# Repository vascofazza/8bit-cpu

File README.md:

# MK1 8bit Computer

Schematics and code for my home-made 8-bit CPU and its companion boards.

Articles about this project:

[Hackaday.com](https://hackaday.com/2020/12/31/diy-8-bit-computer-knows-all-the-tricks/)

[Hackster.io](https://www.hackster.io/news/see-inside-of-a-cpu-with-the-mk1-8bit-computer-14fa9e313c73)

[InformaticaLab.com](https://blog.informaticalab.com/viaggio-allinterno-di-una-cpu-con-il-mk1-8bit-computer/)

## Overview

During the past month, I designed and built a programmable 8-bit CPU from scratch, out of basic series 74LS logic ICs.

This repository contains pictures, schematics, and code for this project and its companion boards.

* V 1.0 assembled:

* V 2.0b assembled:

- Helix Display Interface in action:

* V 1.0 in action:

**DEMO VIDEO (YouTube)**

## Architecture

The MK1 CPU is composed of several modules, all connected trough a common 8-bit BUS, the status of each module is shown by dedicated LEDs. 

- The clock module is designed to allow step-by-step execution; in automatic mode the clock speed can be adjusted from 1Hz up to 32KHz.
- The computer programs are stored in RAM and the CPU can be programmed both manually, by inserting binary machine code through dip-switches, and automatically via a USB PC interface. 
  - The Programming interface is designed to be used in conjunction with an **Arduino Nano** or the **Start9** programming board.
  - The **Start9** programming board allows the loading of multiple programs stored on an on-board flash memory without the aid of an external computer device.
- The Addressable memory space is 1024 byte, data, stack and code spaces are separated, the code address space is not writable. 
- The instructions are variable-length (see **instruction-set [here](https://github.com/vascofazza/8bit-cpu/tree/master/MK1_CPU/programs/lib/mk1.cpu)**) 1 or 2 bytes long (first byte for the opcode, the second one for the argument), there are 4 general purpose registers (`A`, `B`, `C`, `D`) and a  `stack pointer` register for subroutine calls.
- The **A**rithmetic **L**ogic **U**nit has a dedicated register for the second operand and supports the following operations:
  - Addition
  - Subtraction
  - OR
  - AND
  - NOT
  - Left/Right Shift
  - Left/Right Rotation
- The Control Unit combinatory logic is implemented using EEPROMs (see **microcode [here](https://github.com/vascofazza/8bit-cpu/blob/master/MK1_CPU/code/microcode.txt)**) whilst each instruction is realized through a variable number of micro-instruction for a maximum of 6 micro-steps per instruction, including the fetch cycle. The instruction-set  supports both direct and indirect memory access as well as absolute and conditional jumps on carry (`CF`) and zero (`ZF`) ALU flags.
- The computation output can be visualized on a 4-digit display, with a dedicated register, able to represent positive and 2-complement negative numbers both in decimal and hexadecimal format.
- The CPU can be extended thanks to the external BUS interface capable of handling up to 2 peripheral. The communication is bidirectional, the devices can send interrupts to the CPU to notify when new data is available. Interrupts are cleared once the data has been processed.
  - The only available peripheral at the moment is the **Helix** display interface, an ATmega328-driven 2x16 LCD output display.

## Structure

- **MK1 CPU/**:
  - **8bit-computer/**: KiCad project, schematics and PCB design of the **MK1 CPU**.
  - **code/**:
    - microcode.py: generates the binary EEPROM microcode.
    - out_display.py: generates the binary output display EEPROM code.
    - uploader.py: uploads a binary MK1 program to the CPU.
    - mk1_computer_uploader/: Arduino programmer interface sketch.
  - **assembler/**: fork of the hlorenzi's assembler, improved and customized for the MK1
  - **programs/**: a collection of programs for the MK1 CPU plus the assembler definition
- **start9_programming_interface/**: 
  - **programming_interface/**: KiCad project, schematics and PCB design of the **Start9** programming board.
  - **code/start9_programming_interface/**: Arduino code for the programming interface.
- **helix_display_interface/**:
  - **display_interface/**: KiCad project, schematics and PCB design of the **Helix** display interface board.
  - **code/helix_display_interface/**: Arduino code for the display interface.
- **eeprom_programmer/**: KiCad project, schematics and PCB design of a simple Arduino-based eeprom programmer
- **bus_breakout/**: KiCad project, schematics and PCB design of the external bus connector breakout board.

## Changelog

##### V2.0d:

- minor hardware revision
- revisited PCB design
- new memory architecture, code memory section is read-only, stack and data live on separated spaces

##### V2.0b:

- minor hardware revision
- Variable-length instructions (1 or 2 bytes)
- new custom assembler, thanks to https://github.com/hlorenzi/customasm
- few new instructions
- revisited microcode and instruction-set

##### V2.0:

- 4 general purposes registers (A, B, C, D)
- Stack Pointer implemented as an up-down counter
- External interface and interrupt handling
- Output display decodes HEX and ASCII values
- Clock speed multipliers
- Control Unit extended with 4 EEPROMs
- Variable step microcode counter length (each instruction uses the minimum amount of micro-steps)
- revisited microcode and instruction-set

##### V1.0:

- Bugfixes.
- `HL` and `STK` address signals available in the `MAR` dip-switch.

##### V0.1:

- Initial release

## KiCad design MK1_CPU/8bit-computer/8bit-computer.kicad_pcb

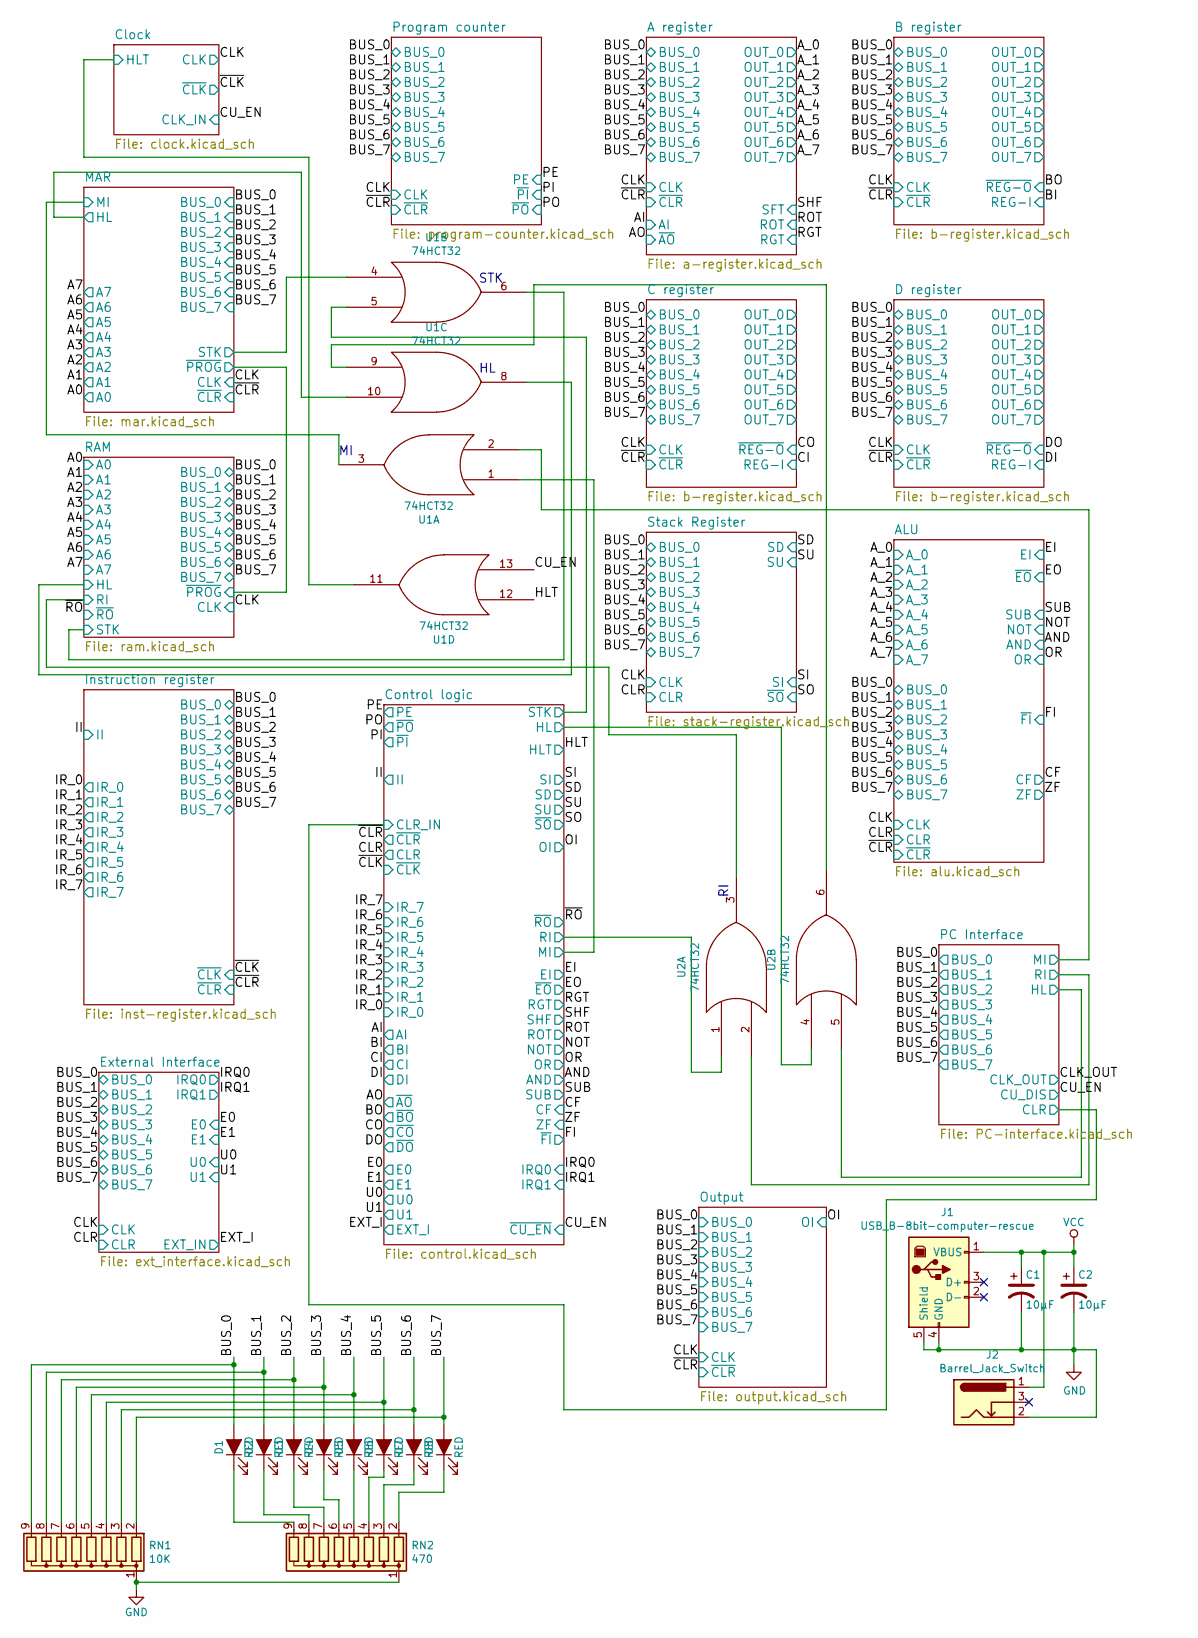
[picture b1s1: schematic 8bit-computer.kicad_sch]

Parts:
C1, C2: 10µF; CP_Radial_D5.0mm_P2.00mm
D1, D2, D3, D4, D5, D6, D7, D8: RED; LED_D3.0mm
J1: USB_B-8bit-computer-rescue; USB_B_OST_USB-B1HSxx_Horizontal
J2: Barrel_Jack_Switch; BarrelJack_Horizontal
RN1: 10K; R_Array_SIP9
RN2: 470; R_Array_SIP9
U1, U2: 74HCT32; DIP-14_W7.62mm

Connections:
/BUS_4: D5.2 (A), RN1.5 (R4); also elsewhere on the board
/BUS_5: D6.2 (A), RN1.4 (R3); also elsewhere on the board
/BUS_6: D7.2 (A), RN1.3 (R2); also elsewhere on the board
/BUS_7: D8.2 (A), RN1.2 (R1); also elsewhere on the board
/Clock/HLT: U1.11; also elsewhere on the board
/Control logic/HL: U2.4; also elsewhere on the board
/Control logic/MI: U1.1; also elsewhere on the board
/Control logic/RI: U2.1; also elsewhere on the board
/Control logic/STK: U1.5; also elsewhere on the board
/MAR/HL: U1.10; also elsewhere on the board
/MAR/MI: U1.3; also elsewhere on the board
/MAR/STK: U1.4; also elsewhere on the board
/PC Interface/CU_DIS: U1.13; also elsewhere on the board
/PC Interface/HL: U2.5; also elsewhere on the board
/PC Interface/MI: U1.2; also elsewhere on the board
/PC Interface/RI: U2.2; also elsewhere on the board
/RAM/HL: U1.8; also elsewhere on the board
/RAM/RI: U2.3; also elsewhere on the board
/RAM/STK: U1.6; also elsewhere on the board
unnamed: D1.1 (K), RN2.9 (R8)
unnamed: D2.1 (K), RN2.8 (R7)
unnamed: D3.1 (K), RN2.7 (R6)
unnamed: D4.1 (K), RN2.6 (R5)
unnamed: D5.1 (K), RN2.5 (R4)
unnamed: D6.1 (K), RN2.4 (R3)
unnamed: D7.1 (K), RN2.3 (R2)
unnamed: D8.1 (K), RN2.2 (R1)
unnamed: U1.9, U2.6

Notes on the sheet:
STK

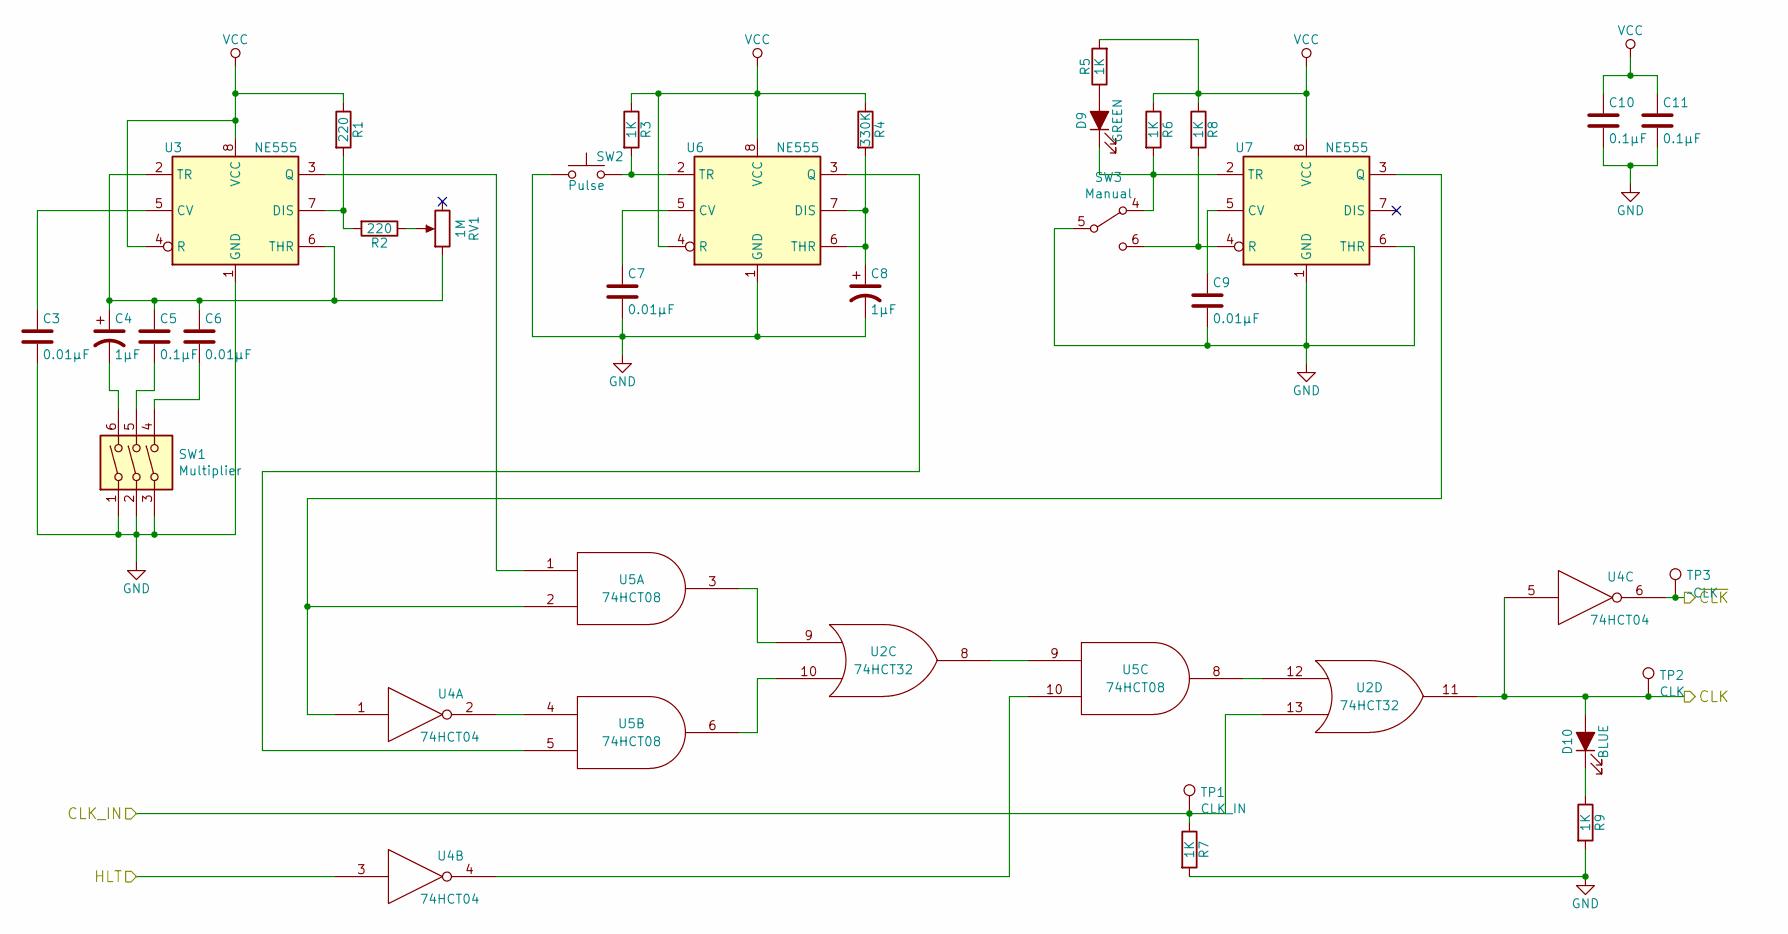
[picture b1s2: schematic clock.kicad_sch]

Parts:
C3, C6, C7, C9: 0.01µF; C_Disc_D4.3mm_W1.9mm_P5.00mm
C4, C8: 1µF; CP_Radial_D5.0mm_P2.00mm
C5, C10, C11: 0.1µF; C_Disc_D4.3mm_W1.9mm_P5.00mm
D9: GREEN; LED_D3.0mm
D10: BLUE; LED_D3.0mm
R1, R2: 220; R_Axial_DIN0207_L6.3mm_D2.5mm_P7.62mm_Horizontal
R3, R5, R6, R7, R8, R9: 1K; R_Axial_DIN0207_L6.3mm_D2.5mm_P7.62mm_Horizontal
R4: 330K; R_Axial_DIN0207_L6.3mm_D2.5mm_P7.62mm_Horizontal
RV1: 1M; Potentiometer_Bourns_PTV09A-1_Single_Vertical
SW1: Multiplier; SW_DIP_SPSTx03_Slide_9.78x9.8mm_W7.62mm_P2.54mm
SW2: Pulse; SW_PUSH_6mm_H5mm
SW3: Manual; SW_NKK_GW12LJP
TP1: CLK_IN; TestPoint_Pad_1.0x1.0mm
TP2: CLK; TestPoint_Pad_1.0x1.0mm
TP3: ~CLK; TestPoint_Pad_1.0x1.0mm
U2: 74HCT32; DIP-14_W7.62mm
U3, U6, U7: NE555; DIP-8_W7.62mm
U4: 74HCT04; DIP-14_W7.62mm
U5: 74HCT08; DIP-14_W7.62mm

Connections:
/Clock/CLK_IN: R7.1, TP1.1, U2.13; also elsewhere on the board
/Clock/HLT: U4.3; also elsewhere on the board
/~CLK: TP3.1, U4.6; also elsewhere on the board
unnamed: C3.1, U3.5 (CV)
unnamed: C4.1, C5.1, C6.1, RV1.1, U3.2 (TR), U3.6 (THR)
unnamed: C4.2, SW1.6
unnamed: C5.2, SW1.5
unnamed: C6.2, SW1.4
unnamed: C7.1, U6.5 (CV)
unnamed: C8.1, R4.2, U6.6 (THR), U6.7 (DIS)
unnamed: C9.1, U7.5 (CV)
unnamed 127: U5.11; also elsewhere on the board
unnamed: D9.1 (K), R6.2, SW3.4 (A), U7.2 (TR)
unnamed: D9.2 (A), R5.1
unnamed: D10.1 (K), R9.1
unnamed: R1.2, R2.2, U3.7 (DIS)
unnamed: R2.1, RV1.2
unnamed: R3.2, SW2.2, U6.2 (TR)
unnamed: R8.2, SW3.6 (C), U7.4 (R)
unnamed: U2.8, U5.9
unnamed: U2.9, U5.3
unnamed: U2.10, U5.6
unnamed: U2.12, U5.8
unnamed: U3.3 (Q), U5.1
unnamed: U4.1, U5.2, U7.3 (Q)
unnamed: U4.2, U5.4
unnamed: U4.4, U5.10
unnamed: U5.5, U6.3 (Q)

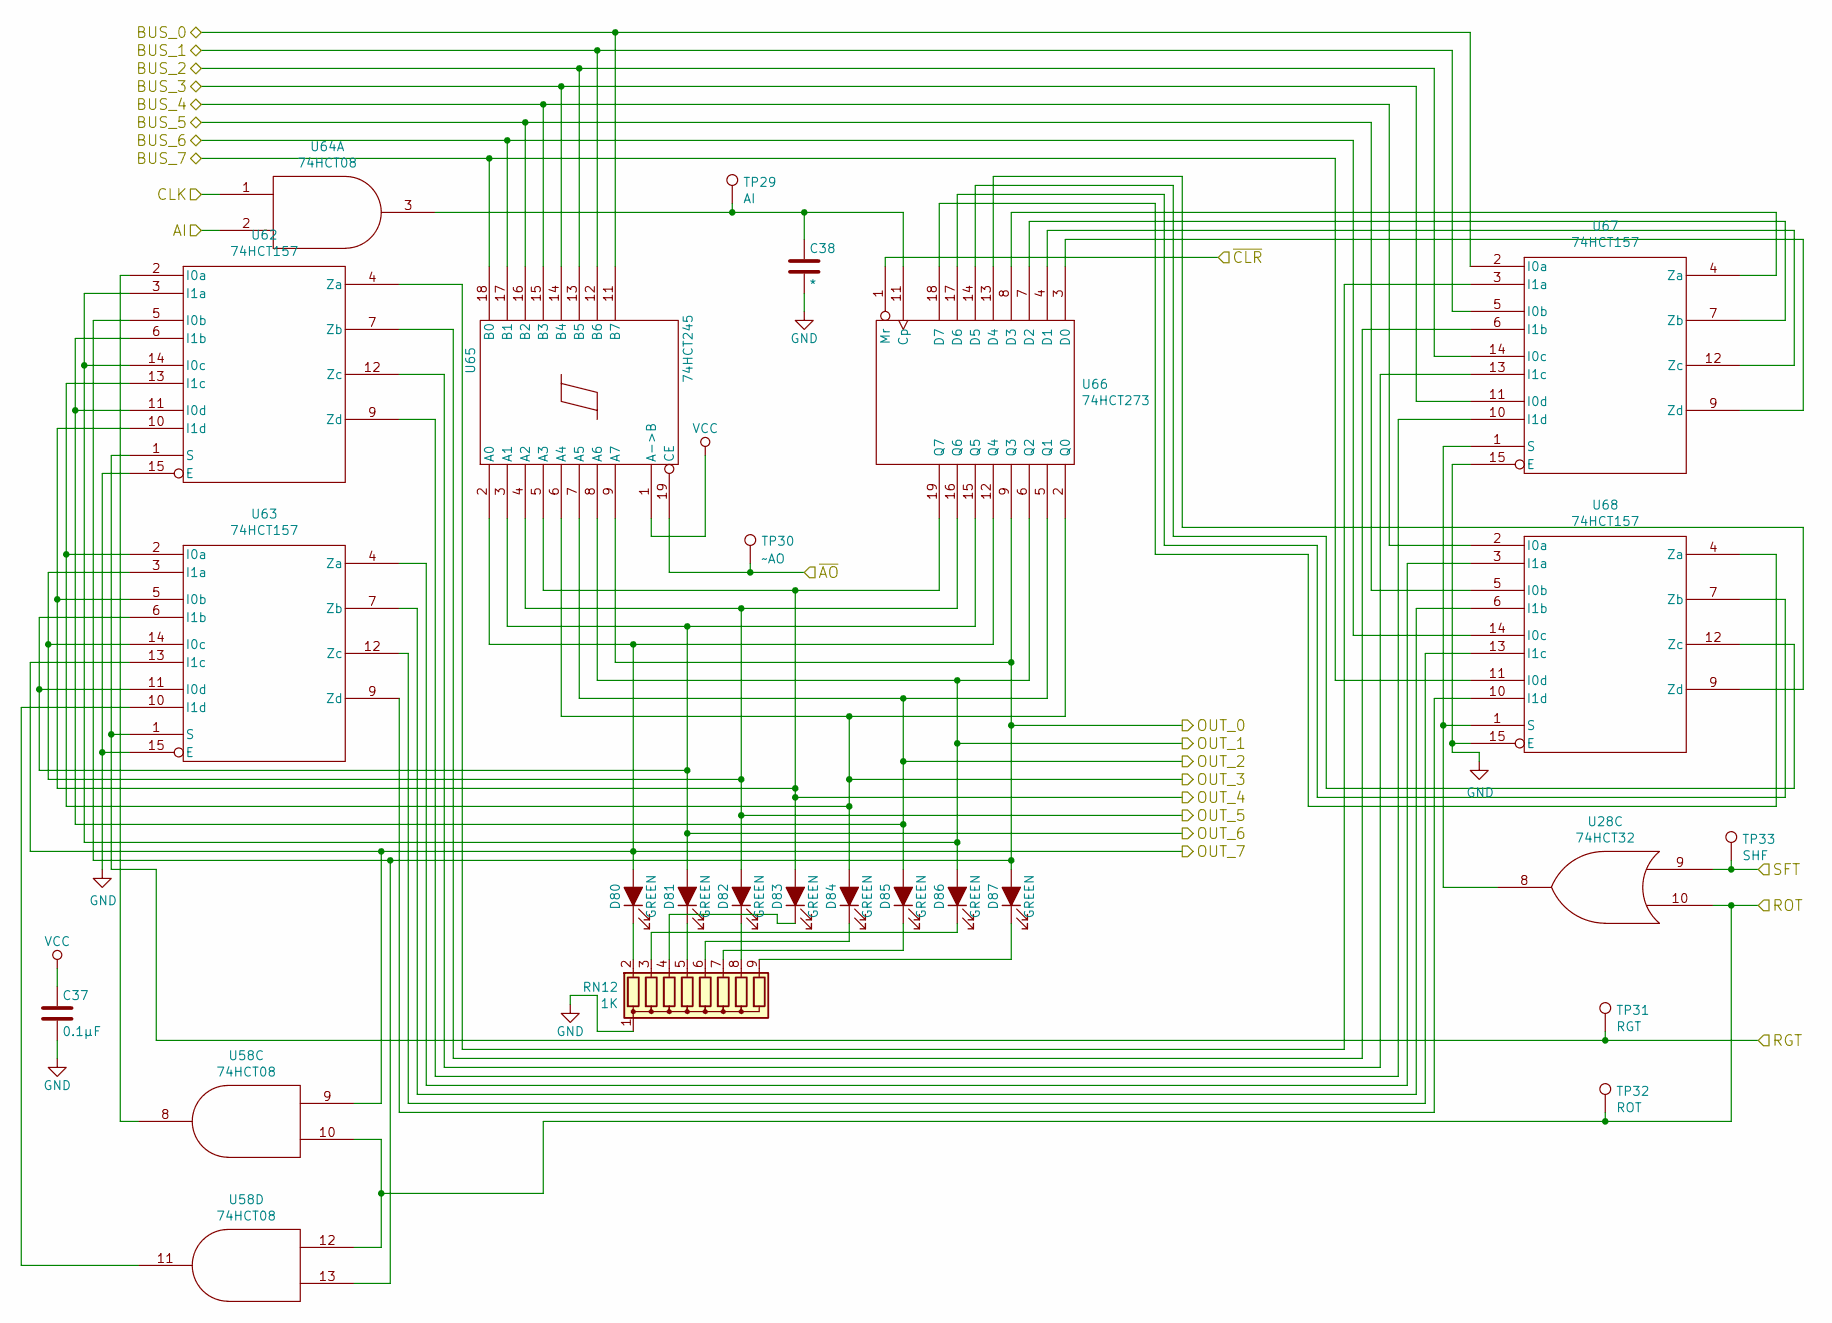
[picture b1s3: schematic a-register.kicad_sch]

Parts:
C37: 0.1µF; C_Disc_D4.3mm_W1.9mm_P5.00mm
C38: *; C_Disc_D4.3mm_W1.9mm_P5.00mm
D80, D81, D82, D83, D84, D85, D86, D87: GREEN; LED_D3.0mm
RN12: 1K; R_Array_SIP9
TP29: AI; TestPoint_Pad_1.0x1.0mm
TP30: ~AO; TestPoint_Pad_1.0x1.0mm
TP31: RGT; TestPoint_Pad_1.0x1.0mm
TP32: ROT; TestPoint_Pad_1.0x1.0mm
TP33: SHF; TestPoint_Pad_1.0x1.0mm
U28: 74HCT32; DIP-14_W7.62mm
U58, U64: 74HCT08; DIP-14_W7.62mm
U62, U63, U67, U68: 74HCT157; DIP-16_W7.62mm
U65: 74HCT245; DIP-20_W7.62mm
U66: 74HCT273; DIP-20_W7.62mm

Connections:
/A register/RGT: TP31.1, U62.1 (S), U63.1 (S); also elsewhere on the board
/A register/ROT: TP32.1, U28.10, U58.10, U58.12; also elsewhere on the board
/A register/~AO: TP30.1, U65.19 (CE); also elsewhere on the board
/A_0: D87.2 (A), U58.13, U62.5 (I0b), U65.9 (A7), U66.9 (Q3); also elsewhere on the board
/A_1: D86.2 (A), U62.3 (I1a), U62.14 (I0c), U65.8 (A6), U66.6 (Q2); also elsewhere on the board
/A_2: D85.2 (A), U62.6 (I1b), U62.11 (I0d), U65.7 (A5), U66.5 (Q1); also elsewhere on the board
/A_3: D84.2 (A), U62.13 (I1c), U63.2 (I0a), U65.6 (A4), U66.2 (Q0); also elsewhere on the board
/A_4: D83.2 (A), U62.10 (I1d), U63.5 (I0b), U65.5 (A3), U66.19 (Q7); also elsewhere on the board
/A_5: D82.2 (A), U63.3 (I1a), U63.14 (I0c), U65.4 (A2), U66.16 (Q6); also elsewhere on the board
/A_6: D81.2 (A), U63.6 (I1b), U63.11 (I0d), U65.3 (A1), U66.15 (Q5); also elsewhere on the board
/A_7: D80.2 (A), U58.9, U63.13 (I1c), U65.2 (A0), U66.12 (Q4); also elsewhere on the board
/BUS_4: U65.15 (B3), U68.2 (I0a); also elsewhere on the board
/BUS_5: U65.16 (B2), U68.5 (I0b); also elsewhere on the board
/BUS_6: U65.17 (B1), U68.14 (I0c); also elsewhere on the board
/BUS_7: U65.18 (B0), U68.11 (I0d); also elsewhere on the board
unnamed: C38.1, TP29.1, U64.3, U66.11 (Cp)
unnamed 137: U64.11; also elsewhere on the board
unnamed: D80.1 (K), RN12.2 (R1)
unnamed: D81.1 (K), RN12.5 (R4)
unnamed: D82.1 (K), RN12.8 (R7)
unnamed: D83.1 (K), RN12.4 (R3)
unnamed: D84.1 (K), RN12.6 (R5)
unnamed: D85.1 (K), RN12.7 (R6)
unnamed: D86.1 (K), RN12.3 (R2)
unnamed: D87.1 (K), RN12.9 (R8)
unnamed: U28.8, U67.1 (S), U68.1 (S)
unnamed: U58.8, U62.2 (I0a)
unnamed: U58.11, U63.10 (I1d)
unnamed: U62.4 (Za), U67.3 (I1a)
unnamed: U62.7 (Zb), U67.6 (I1b)
unnamed: U62.9 (Zd), U67.10 (I1d)
unnamed: U62.12 (Zc), U67.13 (I1c)
unnamed: U63.4 (Za), U68.3 (I1a)
unnamed: U63.7 (Zb), U68.6 (I1b)
unnamed: U63.9 (Zd), U68.10 (I1d)
unnamed: U63.12 (Zc), U68.13 (I1c)
unnamed: U66.3 (D0), U67.9 (Zd)
unnamed: U66.4 (D1), U67.12 (Zc)
unnamed: U66.7 (D2), U67.7 (Zb)
unnamed: U66.8 (D3), U67.4 (Za)
unnamed: U66.13 (D4), U68.9 (Zd)
unnamed: U66.14 (D5), U68.12 (Zc)
unnamed: U66.17 (D6), U68.7 (Zb)
unnamed: U66.18 (D7), U68.4 (Za)

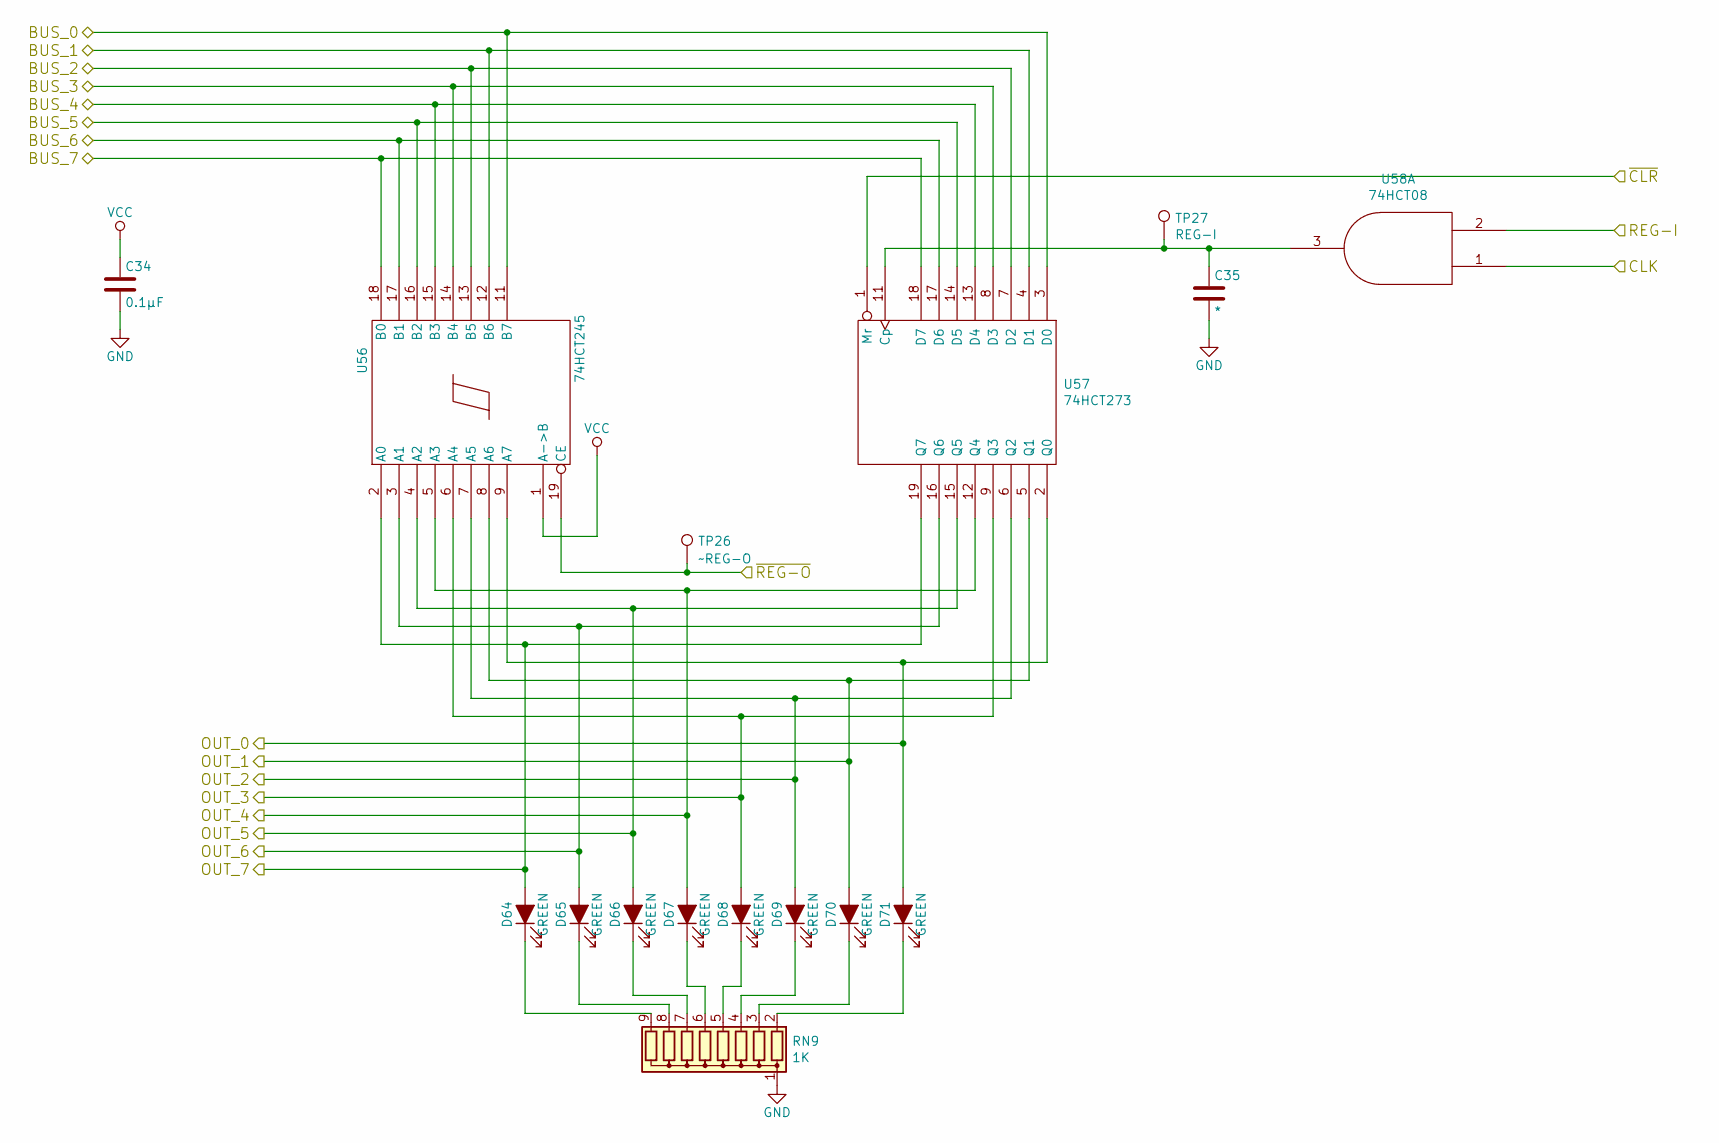
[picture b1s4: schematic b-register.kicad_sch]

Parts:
C34: 0.1µF; C_Disc_D4.3mm_W1.9mm_P5.00mm
C35: *; C_Disc_D4.3mm_W1.9mm_P5.00mm
D64, D65, D66, D67, D68, D69, D70, D71: GREEN; LED_D3.0mm
RN9: 1K; R_Array_SIP9
TP26: ~REG-O; TestPoint_Pad_1.0x1.0mm
TP27: REG-I; TestPoint_Pad_1.0x1.0mm
U56: 74HCT245; DIP-20_W7.62mm
U57: 74HCT273; DIP-20_W7.62mm
U58: 74HCT08; DIP-14_W7.62mm

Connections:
/BUS_4: U56.15 (B3), U57.13 (D4); also elsewhere on the board
/BUS_5: U56.16 (B2), U57.14 (D5); also elsewhere on the board
/BUS_6: U56.17 (B1), U57.17 (D6); also elsewhere on the board
/BUS_7: U56.18 (B0), U57.18 (D7); also elsewhere on the board
/C register/OUT_0: D71.2 (A), U56.9 (A7), U57.2 (Q0)
/C register/OUT_1: D70.2 (A), U56.8 (A6), U57.5 (Q1)
/C register/OUT_2: D69.2 (A), U56.7 (A5), U57.6 (Q2)
/C register/OUT_3: D68.2 (A), U56.6 (A4), U57.9 (Q3)
/C register/OUT_4: D67.2 (A), U56.5 (A3), U57.12 (Q4)
/C register/OUT_5: D66.2 (A), U56.4 (A2), U57.15 (Q5)
/C register/OUT_6: D65.2 (A), U56.3 (A1), U57.16 (Q6)
/C register/OUT_7: D64.2 (A), U56.2 (A0), U57.19 (Q7)
/Control logic/~CO: TP26.1, U56.19 (CE); also elsewhere on the board
unnamed: C35.1, TP27.1, U57.11 (Cp), U58.3
unnamed: D64.1 (K), RN9.9 (R8)
unnamed: D65.1 (K), RN9.8 (R7)
unnamed: D66.1 (K), RN9.7 (R6)
unnamed: D67.1 (K), RN9.6 (R5)
unnamed: D68.1 (K), RN9.5 (R4)
unnamed: D69.1 (K), RN9.4 (R3)
unnamed: D70.1 (K), RN9.3 (R2)
unnamed: D71.1 (K), RN9.2 (R1)

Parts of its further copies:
C12, C42: 0.1µF; C_Disc_D4.3mm_W1.9mm_P5.00mm
C13, C43: *; C_Disc_D4.3mm_W1.9mm_P5.00mm
D11, D12, D13, D14, D15, D16, D17, D18, D127, D128, D129, D130, D131, D132, D133, D134: GREEN; LED_D3.0mm
RN3, RN20: 1K; R_Array_SIP9
TP5, TP41: REG-I; TestPoint_Pad_1.0x1.0mm
U8, U80: 74HCT245; DIP-20_W7.62mm
U9, U81: 74HCT273; DIP-20_W7.62mm

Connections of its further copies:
/B register/OUT_0: D18.2 (A), U8.9 (A7), U9.2 (Q0)
/B register/OUT_1: D17.2 (A), U8.8 (A6), U9.5 (Q1)
/B register/OUT_2: D16.2 (A), U8.7 (A5), U9.6 (Q2)
/B register/OUT_3: D15.2 (A), U8.6 (A4), U9.9 (Q3)
/B register/OUT_4: D14.2 (A), U8.5 (A3), U9.12 (Q4)
/B register/OUT_5: D13.2 (A), U8.4 (A2), U9.15 (Q5)
/B register/OUT_6: D12.2 (A), U8.3 (A1), U9.16 (Q6)
/B register/OUT_7: D11.2 (A), U8.2 (A0), U9.19 (Q7)
/BUS_4: U8.15 (B3), U9.13 (D4), U80.15 (B3), U81.13 (D4); also elsewhere on the board
/BUS_5: U8.16 (B2), U9.14 (D5), U80.16 (B2), U81.14 (D5); also elsewhere on the board
/BUS_6: U8.17 (B1), U9.17 (D6), U80.17 (B1), U81.17 (D6); also elsewhere on the board
/BUS_7: U8.18 (B0), U9.18 (D7), U80.18 (B0), U81.18 (D7); also elsewhere on the board
/Control logic/~BO: U8.19 (CE); also elsewhere on the board
/Control logic/~DO: U80.19 (CE); also elsewhere on the board
/D register/OUT_0: D134.2 (A), U80.9 (A7), U81.2 (Q0)
/D register/OUT_1: D133.2 (A), U80.8 (A6), U81.5 (Q1)
/D register/OUT_2: D132.2 (A), U80.7 (A5), U81.6 (Q2)
/D register/OUT_3: D131.2 (A), U80.6 (A4), U81.9 (Q3)
/D register/OUT_4: D130.2 (A), U80.5 (A3), U81.12 (Q4)
/D register/OUT_5: D129.2 (A), U80.4 (A2), U81.15 (Q5)
/D register/OUT_6: D128.2 (A), U80.3 (A1), U81.16 (Q6)
/D register/OUT_7: D127.2 (A), U80.2 (A0), U81.19 (Q7)
unnamed 127: C13.1, TP5.1, U9.11 (Cp); also elsewhere on the board
unnamed 137: C43.1, TP41.1, U81.11 (Cp); also elsewhere on the board
unnamed: D11.1 (K), RN3.9 (R8)
unnamed: D12.1 (K), RN3.8 (R7)
unnamed: D13.1 (K), RN3.7 (R6)
unnamed: D14.1 (K), RN3.6 (R5)
unnamed: D15.1 (K), RN3.5 (R4)
unnamed: D16.1 (K), RN3.4 (R3)
unnamed: D17.1 (K), RN3.3 (R2)
unnamed: D18.1 (K), RN3.2 (R1)
unnamed: D127.1 (K), RN20.9 (R8)
unnamed: D128.1 (K), RN20.8 (R7)
unnamed: D129.1 (K), RN20.7 (R6)
unnamed: D130.1 (K), RN20.6 (R5)
unnamed: D131.1 (K), RN20.5 (R4)
unnamed: D132.1 (K), RN20.4 (R3)
unnamed: D133.1 (K), RN20.3 (R2)
unnamed: D134.1 (K), RN20.2 (R1)

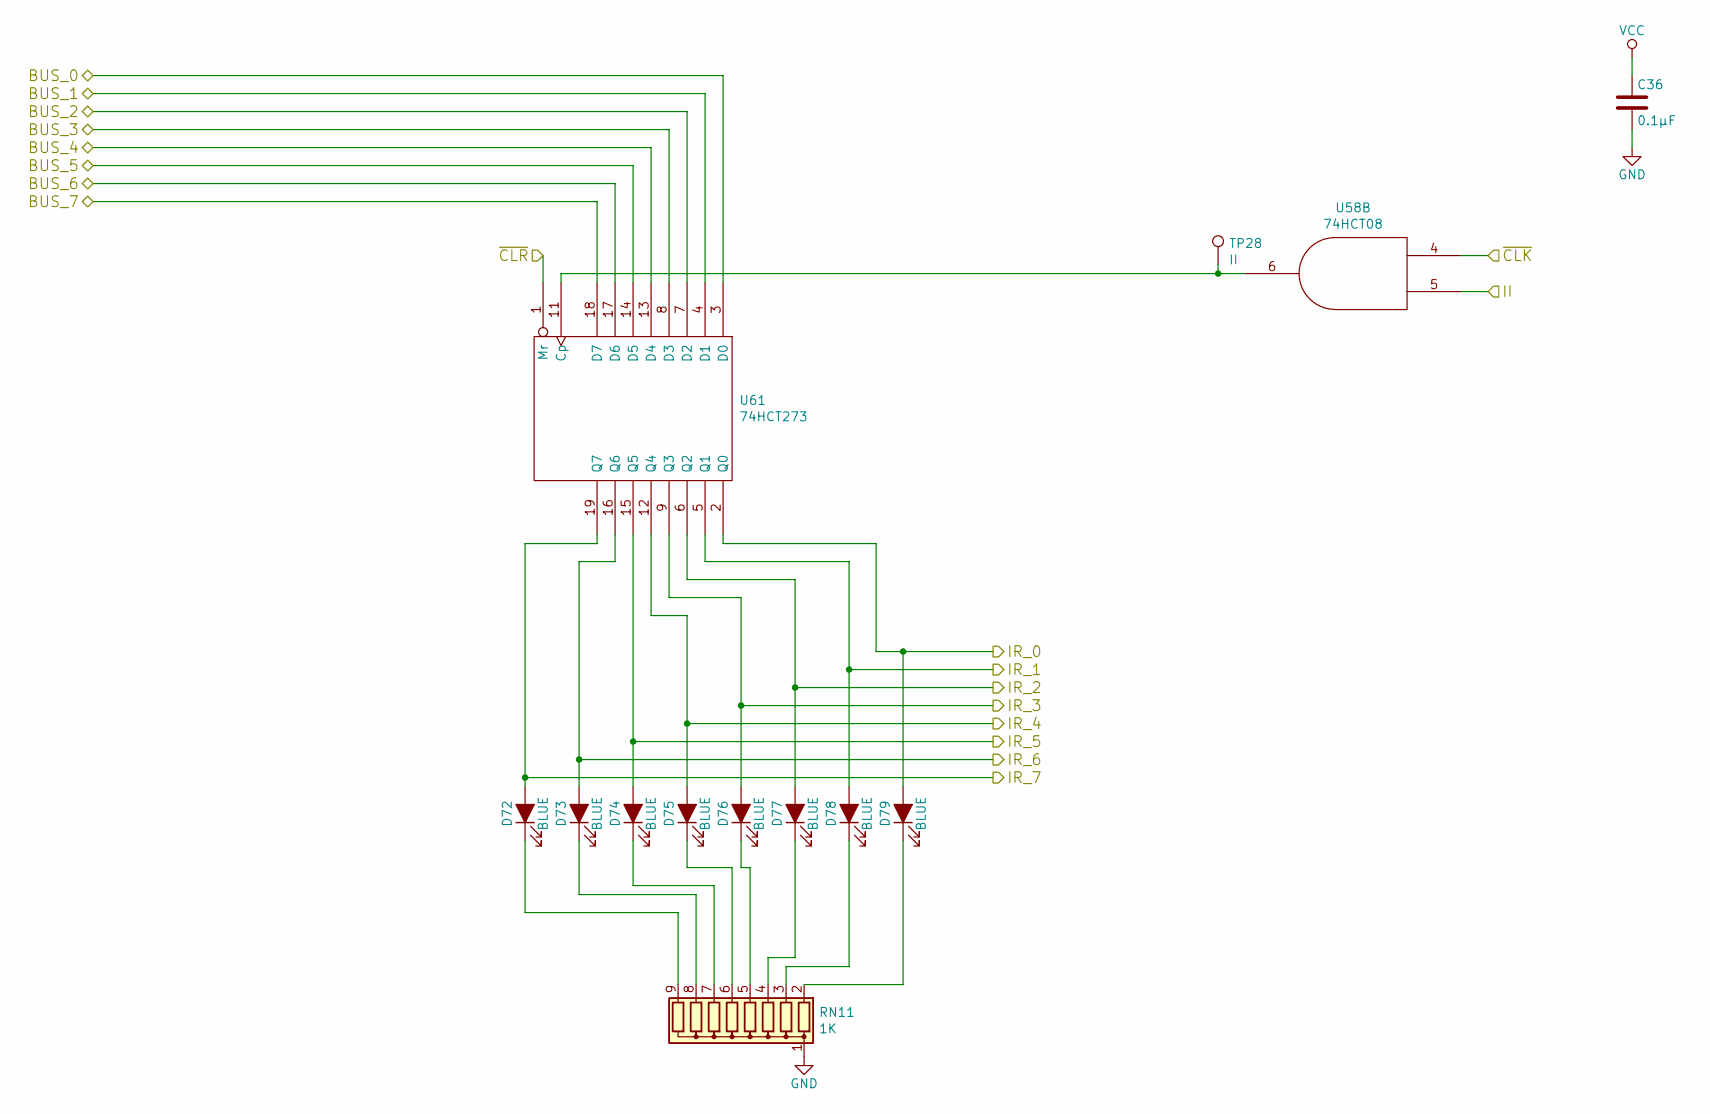
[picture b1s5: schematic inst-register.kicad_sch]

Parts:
C36: 0.1µF; C_Disc_D4.3mm_W1.9mm_P5.00mm
D72, D73, D74, D75, D76, D77, D78, D79: BLUE; LED_D3.0mm
RN11: 1K; R_Array_SIP9
TP28: II; TestPoint_Pad_1.0x1.0mm
U58: 74HCT08; DIP-14_W7.62mm
U61: 74HCT273; DIP-20_W7.62mm

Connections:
/BUS_4: U61.13 (D4); also elsewhere on the board
/BUS_5: U61.14 (D5); also elsewhere on the board
/BUS_6: U61.17 (D6); also elsewhere on the board
/BUS_7: U61.18 (D7); also elsewhere on the board
/Control logic/II: U58.5; also elsewhere on the board
/IR_0: D79.2 (A), U61.2 (Q0); also elsewhere on the board
/IR_1: D78.2 (A), U61.5 (Q1); also elsewhere on the board
/IR_2: D77.2 (A), U61.6 (Q2); also elsewhere on the board
/IR_3: D76.2 (A), U61.9 (Q3); also elsewhere on the board
/IR_4: D75.2 (A), U61.12 (Q4); also elsewhere on the board
/IR_5: D74.2 (A), U61.15 (Q5); also elsewhere on the board
/IR_6: D73.2 (A), U61.16 (Q6); also elsewhere on the board
/IR_7: D72.2 (A), U61.19 (Q7); also elsewhere on the board
/~CLK: U58.4; also elsewhere on the board
unnamed: D72.1 (K), RN11.9 (R8)
unnamed: D73.1 (K), RN11.8 (R7)
unnamed: D74.1 (K), RN11.7 (R6)
unnamed: D75.1 (K), RN11.6 (R5)
unnamed: D76.1 (K), RN11.5 (R4)
unnamed: D77.1 (K), RN11.4 (R3)
unnamed: D78.1 (K), RN11.3 (R2)
unnamed: D79.1 (K), RN11.2 (R1)
unnamed: TP28.1, U58.6, U61.11 (Cp)

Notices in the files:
MK1_CPU/8bit-computer/old.kicad_pcb:
©2018 Ben Eater — Rev A
start9_programming_interface/programming_interface/programming_interface.kicad_pcb:
2020 copyright Federico Scozzafava https://github.com/vascofazza/8bit_cpu
